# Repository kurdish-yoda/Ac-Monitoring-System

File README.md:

# Ac Monitoring System

Device for monitoring 3 phase AC current. 

## Description
Ability to sample 3 phases at time checking for power losses on individual phases, which should trigger an alert over the GSM 
network. In the event of a complete power out an alarm will be switched on, which will then fasilitate the input of generator volatage.

## Features
- Onion Omega 2+
- SIM800L Module 
- 16 bit ADC
- battery input capabilities
- generator input with surge protection

## Pictures

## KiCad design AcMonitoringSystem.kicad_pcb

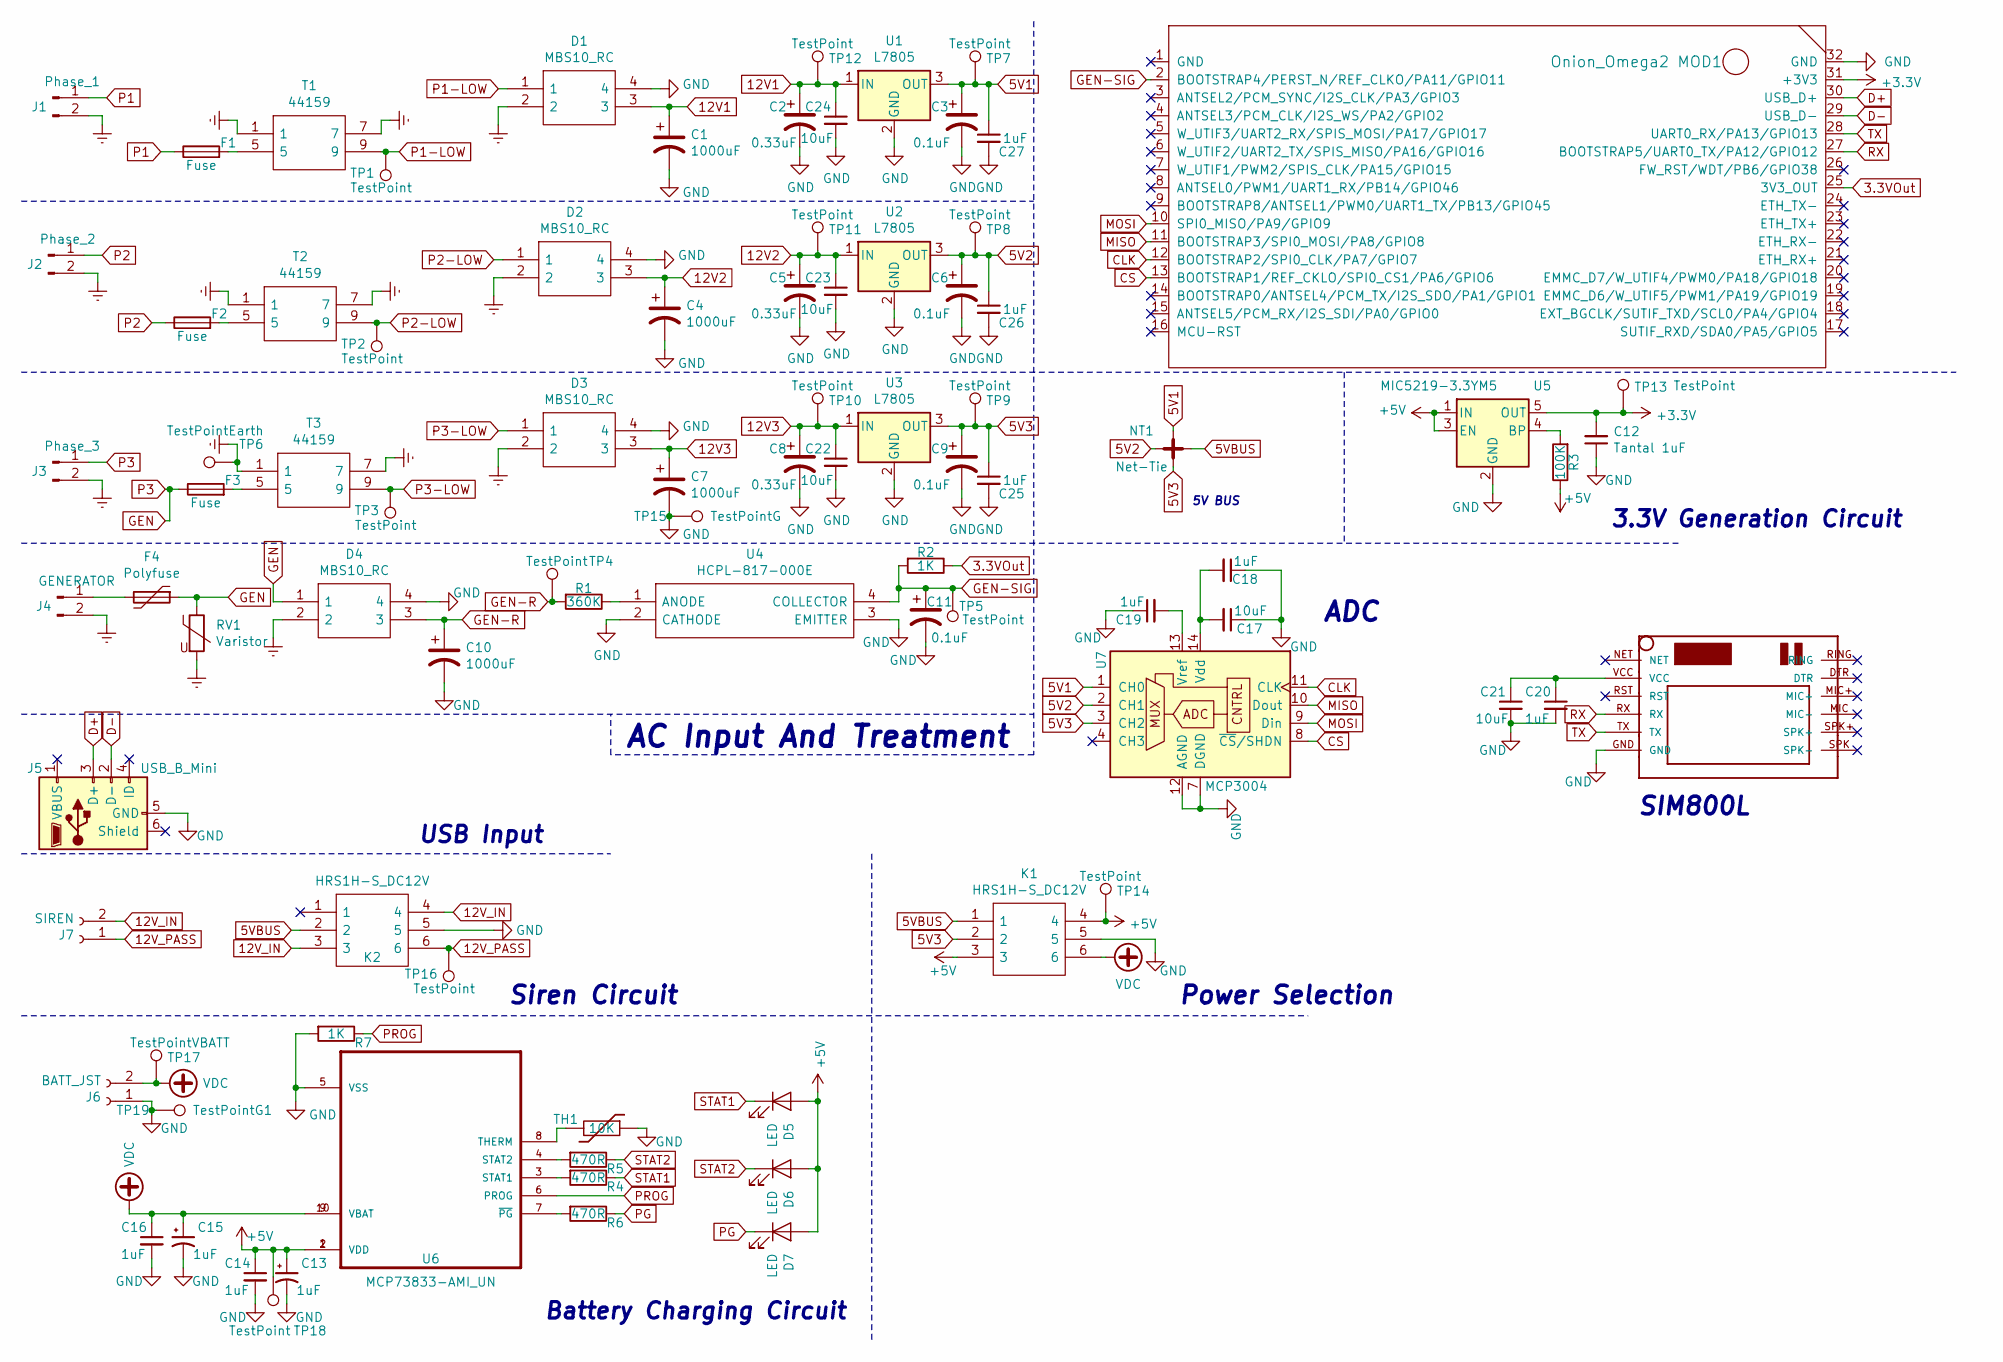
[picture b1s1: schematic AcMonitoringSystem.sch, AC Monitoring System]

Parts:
C1, C4, C7, C10: 1000uF; CP_Radial_D10.0mm_P5.00mm
C2, C5, C8: 0.33uF; CP_Radial_D4.0mm_P1.50mm
C3, C6, C9, C11: 0.1uF; CP_Radial_D4.0mm_P1.50mm
C12: Tantal 1uF; C_1206_3216Metric_Pad1.42x1.75mm_HandSolder
C13, C15: 1uF; CP_Radial_D5.0mm_P2.00mm
C14, C16, C18, C19, C20, C25, C26, C27: 1uF; C_0805_2012Metric_Pad1.15x1.40mm_HandSolder
C17, C21, C22, C23, C24: 10uF; C_0805_2012Metric_Pad1.15x1.40mm_HandSolder
D1, D2, D3, D4: MBS10_RC; SOP240P690X290-4N; Manufacturer_Part_Number MBS10 RC
D5, D6, D7: LED; LED_SK6812MINI_PLCC4_3.5x3.5mm_P1.75mm
F1, F2, F3: Fuse; Fuseholder_TR5_Littelfuse_No560_No460
F4: Polyfuse; C_Disc_D4.3mm_W1.9mm_P5.00mm
J1: Phase_1; TerminalBlock_Phoenix_MKDS-1,5-2_1x02_P5.00mm_Horizontal
J2: Phase_2; TerminalBlock_Phoenix_MKDS-1,5-2_1x02_P5.00mm_Horizontal
J3: Phase_3; TerminalBlock_Phoenix_MKDS-1,5-2_1x02_P5.00mm_Horizontal
J4: GENERATOR; TerminalBlock_Phoenix_MKDS-1,5-2_1x02_P5.00mm_Horizontal
J5: USB_B_Mini; USB_Micro-B_Wuerth_629105150521_CircularHoles
J6: BATT_JST; JST_EH_B2B-EH-A_1x02_P2.50mm_Vertical
J7: SIREN; TerminalBlock_Phoenix_MKDS-1,5-2_1x02_P5.00mm_Horizontal
K1, K2: HRS1H-S_DC12V; HRS1H-S; Manufacturer_Part_Number HRS1H-S DC5V
MOD1: Onion_Omega2; ONION_OMEGA2
NT1: Net-Tie; NetTie-4_THT_Pad1.0mm
R1: 360K; R_0805_2012Metric_Pad1.15x1.40mm_HandSolder
R2, R7: 1K; R_0805_2012Metric_Pad1.15x1.40mm_HandSolder
R3: 100K; R_0805_2012Metric_Pad1.15x1.40mm_HandSolder
R4, R5, R6: 470R; R_0805_2012Metric_Pad1.15x1.40mm_HandSolder
RV1: Varistor; RV_Disc_D9mm_W3.3mm_P5mm
T1, T2, T3: 44159; Manufacturer_Part_Number 44159
TH1: 10K; R_0402_1005Metric
TP1, TP2, TP3, TP4, TP5, TP7, TP8, TP9, TP10, TP11, TP12, TP13, TP14, TP16, TP18: TestPoint; TestPoint_Pad_2.0x2.0mm
TP6: TestPointEarth; TestPoint_Pad_4.0x4.0mm
TP15: TestPointG; TestPoint_Pad_4.0x4.0mm
TP17: TestPointVBATT; TestPoint_Pad_4.0x4.0mm
TP19: TestPointG1; TestPoint_Pad_4.0x4.0mm
U1, U2, U3: L7805; TO-252-2
U4: HCPL-817-000E; DIP762W60P254L460H400Q4N; Manufacturer_Part_Number HCPL-817-000E; Mouser Part Number 630-HCPL-817-000E
U5: MIC5219-3.3YM5; SOT-23-5
U6: MCP73833-AMI_UN; MSOP-10_3x3mm_P0.5mm
U7: MCP3004; TSSOP-14_4.4x5mm_P0.65mm
U8: SIM800LMODULE

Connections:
3.3VOut: MOD1.25 (3V3_OUT), R2.1
5V1: C3.1, C27.1, NT1.3, TP7.1, U1.3 (OUT), U7.1 (CH0)
5V2: C6.1, C26.1, NT1.1, TP8.1, U2.3 (OUT), U7.2 (CH1)
5V3: C9.1, C25.1, K1.2, NT1.4, TP9.1, U3.3 (OUT), U7.3 (CH2)
5VBUS: K1.1, K2.2, NT1.2
12V1: C1.1, C2.1, C24.1, D1.3, TP12.1, U1.1 (IN)
12V2: C4.1, C5.1, C23.1, D2.3, TP11.1, U2.1 (IN)
12V3: C7.1, C8.1, C22.1, D3.3, TP10.1, U3.1 (IN)
12V_IN: J7.2, K2.3, K2.4
12V_PASS: J7.1, K2.6, TP16.1
+3V3: C12.2, MOD1.31 (+3V3), TP13.1, U5.5 (OUT)
+5V: C13.1, C14.1, D5.2 (A), D6.2 (A), D7.2 (A), K1.3, K1.4, R3.1, TP14.1, TP18.1, U5.1 (IN), U5.3 (EN), U6.1 (VDD), U6.2 (VDD)
CLK: MOD1.12 (BOOTSTRAP2/SPI0_CLK/PA7/GPIO7), U7.11 (CLK)
CS: MOD1.13 (BOOTSTRAP1/REF_CKLO/SPI0_CS1/PA6/GPIO6), U7.8 (~CS~/SHDN)
D+: J5.3 (D+), MOD1.30 (USB_D+)
D-: J5.2 (D-), MOD1.29 (USB_D-)
Earth: D1.2, D2.2, D3.2, D4.2, J1.2, J2.2, J3.2, J4.2, RV1.2, T1.1, T1.7, T2.1, T2.7, T3.1, T3.7, TP6.1
GEN: D4.1, F3.1, F4.1, J3.1, RV1.1
GEN-R: C10.1, D4.3, R1.2, TP4.1
GEN-SIG: C11.1, MOD1.2 (BOOTSTRAP4/PERST_N/REF_CLKO/PA11/GPIO11), R2.2, TP5.1, U4.4 (COLLECTOR)
GND: C1.2, C2.2, C3.2, C4.2, C5.2, C6.2, C7.2, C8.2, C9.2, C10.2, C11.2, C12.1, C13.2, C14.2, C15.2, C16.2, C17.1, C18.1, C19.1, C20.2, C21.2, C22.2, C23.2, C24.2, C25.2, C26.2, C27.2, D1.4, D2.4, D3.4, D4.4, J5.5 (GND), J6.1, K1.5, K2.5, MOD1.32 (GND), R7.2, TH1.1, TP15.1, TP19.1, U1.2 (GND), U2.2 (GND), U3.2 (GND), U4.2 (CATHODE), U4.3 (EMITTER), U5.2 (GND), U6.5 (VSS), U7.7 (DGND), U7.12 (AGND), U8.GND
MISO: MOD1.11 (BOOTSTRAP3/SPI0_MOSI/PA8/GPIO8), U7.10 (Dout)
MOSI: MOD1.10 (SPI0_MISO/PA9/GPIO9), U7.9 (Din)
unnamed: C17.2, C18.2, U7.14 (Vdd)
unnamed: C19.2, U7.13 (Vref)
unnamed: C20.1, C21.1, U8.VCC
unnamed: F1.2, T1.5
unnamed: F2.2, T2.5
unnamed: F3.2, T3.5
unnamed: F4.2, J4.1
unnamed: R1.1, U4.1 (ANODE)
unnamed: R3.2, U5.4 (BP)
unnamed: R4.2, U6.3 (STAT1)
unnamed: R5.2, U6.4 (STAT2)
unnamed: R6.2, U6.7 (~PG~)
unnamed: TH1.2, U6.8 (THERM)
P1: F1.1, J1.1
P1-LOW: D1.1, T1.9, TP1.1
P2: F2.1, J2.1
P2-LOW: D2.1, T2.9, TP2.1
P3-LOW: D3.1, T3.9, TP3.1
PG: D7.1 (K), R6.1
PROG: R7.1, U6.6 (PROG)
RX: MOD1.27 (BOOTSTRAP5/UART0_TX/PA12/GPIO12), U8.RX
STAT1: D5.1 (K), R4.1
STAT2: D6.1 (K), R5.1
TX: MOD1.28 (UART0_RX/PA13/GPIO13), U8.TX
VDC: C15.1, C16.1, J6.2, K1.6, TP17.1, U6.9 (VBAT), U6.10 (VBAT)

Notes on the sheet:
AC Input And Treatment
5V BUS
Battery Charging Circuit
USB Input
3.3V Generation Circuit
Siren Circuit
Power Selection
ADC
SIM800L

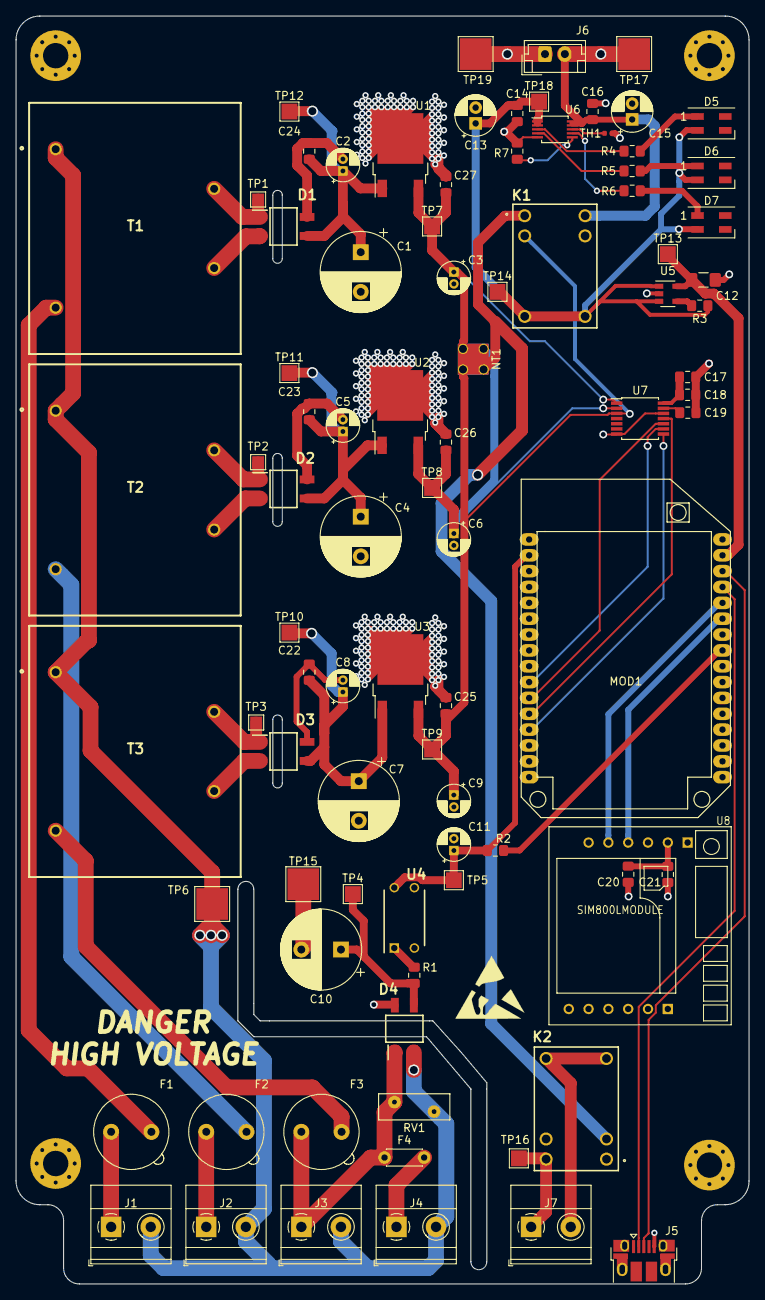
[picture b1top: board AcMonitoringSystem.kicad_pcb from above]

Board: 2 copper layers, 92.5 x 160.0 mm, 92 parts (0 on the bottom side), 48 nets.

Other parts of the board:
H1, H2, H4, H4#2: MountingHole; MountingHole_3.2mm_M3_Pad_Via

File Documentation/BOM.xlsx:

Line No. | Order Code | RoHS Compliant? | Your Part No | Notes | Qty | Manufacturer Part Number | Manufacturer Name | Manufacturer / Description | Availability | Unit Price | Line Price | Discount Price
1 | 1004398 | RoHS: YES / PHTHALATES: YES | RV1 | MOV | 2 | B72210S0381K101 | EPCOS | EPCOS TVS Varistor, MOV, 385 V, 505 V, StandarD Series, 1.025 kV, Disc 10mm, Me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 | 511 | 0.42199999999999999 | 0.84
2 | 2752772 | RoHS: YES / PHTHALATES: YES | F4 | PolyFuse | 2 | LVR012S | LITTELFUSE | LITTELFUSE PPTC Resettable Fuse, Through Hole, PolySwitch LVR Series, 120 mA, 3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 | 474 | 0.61699999999999999 | 1.23
3 | 1566069 | RoHS: YES / PHTHALATES: YES | F1, F2, F3 |  | 6 | MCMET 630MA 250V | MULTICOMP PRO | MULTICOMP PRO Fuse, PCB Leaded, 630 mA, 250 VAC, Slow Blow, Radial Leaded | 937149 | 7.1499999999999994E-2 | 0.43
4 | 2510249 | RoHS: YES / PHTHALATES: YES | U5 |  | 2 | MIC5216-3.3YM5-TR | MICROCHIP | MICROCHIP Fixed LDO Voltage Regulator, 2.5V to 12V, 300mV Dropout, 3.3Vout, 500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 | 2392 | 0.96 | 1.92
5 | 1457409 | RoHS: YES / PHTHALATES: YES | C12 |  | 5 | T491A105K025AT | KEMET | KEMET Surface Mount Tantalum Capacitor, 1 µF, 25 V, 1206 [3216 Metric], T491 Se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 | 20198 | 0.224 | 1.1200000000000001
6 | 2447662 | RoHS: Y-EX / PHTHALATES: YES | R4, R5, R6 |  | 10 | MCWR08X4700FTL | MULTICOMP PRO | MULTICOMP PRO SMD Chip Resistor, 0805 [2012 Metric], 470 ohm, MCWR Series, 150 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 | 57352 | 6.7999999999999996E-3 | 7.0000000000000007E-2
7 | 1649009 | RoHS: YES / PHTHALATES: YES | D5, D6, D7 |  | 10 | LM1-EWN1-11-N2-00001 | CREE | CREE LED, White, SMD, 30 mA, 3.6 V, 1.4 cd | 8389 | 0.16600000000000001 | 1.66
8 | 2668482 | RoHS: YES / PHTHALATES: YES | J5 |  | 10 | 10118194-0001LF | AMPHENOL ICC | AMPHENOL ICC USB Connector, Micro USB Type B, USB 2.0, Receptacle, 5 Ways, Surf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 | 27380 | 0.249 | 2.4900000000000002
9 | 2747640 | RoHS: YES / PHTHALATES: YES | U1, U2, U3 |  | 10 | TS78M05CP ROG | TAIWAN SEMICONDUCTOR | TAIWAN SEMICONDUCTOR LINEAR VOLT REG, 5V, 500MA, TO-252-3 | 4929 | 0.56000000000000005 | 5.6
10 | 7355572 | RoHS: YES / PHTHALATES: YES | D1, D2, D3, D4 |  | 10 | MBS10 | TAIWAN SEMICONDUCTOR | TAIWAN SEMICONDUCTOR Bridge Rectifier Diode, Miniature, Single Phase, 1 kV, 500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 | 1171 | 0.13300000000000001 | 1.33
11 | 2901332 | RoHS: YES / PHTHALATES: YES | C2, C5, C8 |  | 6 | SS063M0R33B1F-0407 | TEAPO | TEAPO Electrolytic Capacitor, 0.33 µF, 63 V, SS Series, ± 20%, Radial Leaded, 4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 | 128 | 3.9300000000000002E-2 | 0.24
12 | 1870945 | RoHS: YES / PHTHALATES: YES | C3, C6, C9, C11 |  | 8 | MCUMR50V104M4X5 | MULTICOMP PRO | MULTICOMP PRO Electrolytic Capacitor, 0.1 µF, 50 V, MCUMR Series, ± 20%, Radial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 | 1455 | 6.8400000000000002E-2 | 0.55000000000000004
13 | 2579786 | RoHS: Y-EX / PHTHALATES: YES | J1, J2, J3, J4, J7 |  | 10 | 20020316-G021B01LF | AMPHENOL ICC | AMPHENOL ICC Wire-To-Board Terminal Block, 5 mm, 2 Ways, 28 AWG, 12 AWG, 2.5 mm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 | 410 | 0.26800000000000002 | 2.68
14 | 1593462 | RoHS: YES / PHTHALATES: YES | U8 | Pins For module | 10 | 2212S-06SG-85 | MULTICOMP | MULTICOMP Board-To-Board Connector, 2.54 mm, 6 Contacts, Receptacle, 2212S Seri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 | 55168 | 0.11899999999999999 | 1.19
15 | 1689063 | RoHS: YES / PHTHALATES: TBA | T1, T2, T3 |  | 6 | 44159 | MYRRA | MYRRA Isolation Transformer, EI 30 x 18, 2.3 VA, 12V, 192 mA, 1 x 230V, PCB MOU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 | 69 | 3.73 | 22.38
16 | 2456121 | RoHS: YES / PHTHALATES: YES | TH1 | termistor | 10 | NCP15XH103F03RC | MURATA | MURATA Thermistor, NTC, 10 kohm, NCP Series, 3380 K, SMD, 0402 [1005 Metric] | 17110 | 9.1600000000000001E-2 | 0.92
17 | 2409048 | RoHS: YES / PHTHALATES: YES | C14, C16, C25, C26, C27, C18, C19, C20 |  | 20 | C0805C105K8RACTU | KEMET | KEMET SMD Multilayer Ceramic Capacitor, 1 µF, 10 V, 0805 [2012 Metric], ± 10%, 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 | 9637 | 5.7200000000000001E-2 | 1.1399999999999999
18 | 3013457 | RoHS: YES / PHTHALATES: YES | C24, C23, C22, C17, C21 |  | 10 | CL21A106MQFNNNE | SAMSUNG ELECTRO-MECHANICS | SAMSUNG ELECTRO-MECHANICS SMD Multilayer Ceramic Capacitor, 10 µF, 6.3 V, 0805 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 | 25855 | 0.09 | 0.9
19 | 1593463 | RoHS: YES / PHTHALATES: YES | MOD1 | Pins for omega | 10 | 2212S-08SG-85 | MULTICOMP | MULTICOMP Board-To-Board Connector, 2.54 mm, 8 Contacts, Receptacle, 2212S Seri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 | 53801 | 0.16 | 1.6
20 | 1523365 | RoHS: YES / PHTHALATES: YES | U7 |  | 2 | MCP3004-I/ST | MICROCHIP | MICROCHIP Analogue to Digital Converter, 10 bit, 200 kSPS, Pseudo Differential,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 | 186 | 1.73 | 3.46
21 | 1332160 | RoHS: YES / PHTHALATES: YES | U6 |  | 2 | MCP73833-AMI/UN | MICROCHIP | MICROCHIP Battery Charger for 1 Cell of Li-Ion, Li-Pol battery, 6V input, 4.2V 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 | 1308 | 0.72 | 1.44
22 | 9451129 | RoHS: YES / PHTHALATES: YES | C10, C7, C4, C1 |  | 8 | MCGPR16V108M10X16 | MULTICOMP PRO | MULTICOMP PRO Electrolytic Capacitor, 1000 µF, 16 V, MCGPR Series, ± 20%, Radia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 | 28797 | 0.20899999999999999 | 1.67
23 | 1236655 | RoHS: YES / PHTHALATES: YES | C13, C15 |  | 5 | MCNP16V105M5X11 | MULTICOMP PRO | MULTICOMP PRO Electrolytic Capacitor, 1 µF, 16 V, MCNP Series, ± 20%, Radial Le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 | 849 | 4.0599999999999997E-2 | 0.2
24 | 2447551 | RoHS: Y-EX / PHTHALATES: YES | R3 |  | 10 | MCWR08X1003FTL | MULTICOMP PRO | MULTICOMP PRO SMD Chip Resistor, 0805 [2012 Metric], 100 kohm, MCWR Series, 150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 | 213726 | 6.7000000000000002E-3 | 7.0000000000000007E-2
25 | 9480269 | RoHS: YES / PHTHALATES: YES | K1, K2 |  | 5 | HRS1H-S DC5V | MULTICOMP | MULTICOMP Signal Relay, 5 VDC, SPDT, 3 A, HRS1 Series, Through Hole | 13186 | 1.06 | 5.3
26 | 1738959 | RoHS: Y-EX / PHTHALATES: YES | R2, R7 |  | 10 | CRCW08051K00FKEAHP. | VISHAY | VISHAY SMD Chip Resistor, 0805 [2012 Metric], 1 kohm, CRCW-HP e3 Series, 150 V,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 | 19940 | 0.224 | 2.2400000000000002
27 | 1244544 | RoHS: YES / PHTHALATES: YES | U4 |  | 5 | HCPL-817-000E | BROADCOM | BROADCOM Optocoupler, Transistor Output, 1 Channel, DIP, 4 Pins, 50 mA, 5 kV, 5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 | 22749 | 0.31 | 1.55
28 | 2426668 | RoHS: Y-EX / PHTHALATES: TBA | R1 |  | 10 | MCHP122WF3603T4E | MULTICOMP PRO | MULTICOMP PRO SMD Chip Resistor, 2512 [6432 Metric], 360 kohm, MCHP12 Series, 2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 | 3288 Available until stock is exhausted | 2.1600000000000001E-2 | 0.22
29 | 1516289 | RoHS: YES / PHTHALATES: YES | J6 |  | 100 | S2B-XH-A (LF)(SN) | JST (JAPAN SOLDERLESS TERMINALS) | JST (JAPAN SOLDERLESS TERMINALS) Wire-To-Board Connector, Right Angle, 2.5 mm, 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 | 54943 | 9.5000000000000001E-2 | 9.5
 |  |  |  |  |  |  | Sub Total | 73.94
 |  |  |  |  |  |  | Goods Total | 73.94
 |  |  |  |  |  |  | Delivery | 0
 |  |  |  |  |  |  | VAT | Unknown
 |  |  |  |  |  |  | Total | 73.94

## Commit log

2020-02-12 bulk pcb files
2020-02-12 edited
2020-03-25 last add for this version
